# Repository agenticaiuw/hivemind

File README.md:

# Agentic Gadget

Unified monorepo for the Agentic Gadget hardware, firmware, local agent, cloud
relay, and Bluetooth audio bridge.

## Layout

- `firmware/nrf9160` — nRF9160 DK firmware (Zephyr/NCS)
- `firmware/esp32-airpods-bridge` — HUZZAH32 Bluetooth A2DP audio bridge
- `software/ai-pendant-simulator` — local Mac agent, cloud relay, and simulator
- `software/dashboard-sveltekit` — Mission Control dashboard (Cloudflare Worker)
- `hardware` — datasheets, electrical design, and KiCad sources
- `docs` — build guides and architecture notes

## Local agent

Keep private credentials in the repo-root `.env` (see `.env.example`). That file
is ignored by Git.

```sh
cd software/ai-pendant-simulator
npm install
npm test
npm run agent
```

## nRF9160 firmware

Build from `firmware/nrf9160` using the installed Nordic toolchain (NCS under
`/opt/nordic/ncs`). Build directories are intentionally not stored in this
repository. Private Kconfig values belong in the ignored
`firmware/nrf9160/secrets.conf` file and must be included with
`-DEXTRA_CONF_FILE=secrets.conf` when creating a fresh build.

```sh
source firmware/nrf9160/scripts/env.sh          # puts west/nrfutil on PATH
firmware/nrf9160/scripts/flash.sh --check       # verify probe + tools
# build (see docs/How_This_System_Runs.md), then:
firmware/nrf9160/scripts/flash.sh               # nrfutil → J-Link 960036581
```

ESP32 bridge: `firmware/esp32-airpods-bridge/flash.sh` (PlatformIO in `.venv`).

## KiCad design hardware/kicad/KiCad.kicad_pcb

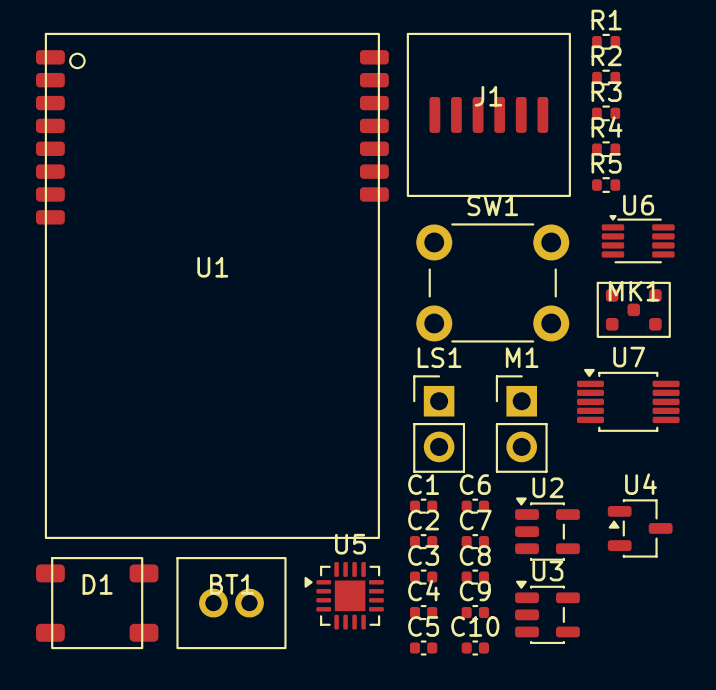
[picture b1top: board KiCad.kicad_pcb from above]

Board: 2 copper layers, 29 parts (0 on the bottom side), 26 nets, no tracks yet.

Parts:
BT1: LiPo_3V7; JST_PH_S2B
C1, C2: 4.7uF; C_0402_1005Metric
C3: 100uF; C_0402_1005Metric
C4: 10uF; C_0402_1005Metric
C5, C6, C8, C9: 1uF; C_0402_1005Metric
C7, C10: 0.1uF; C_0402_1005Metric
D1: SK6812
J1: USB4085_USB_C; USB4085-GF-A
LS1: Speaker_8ohm; PinHeader_1x02_P2.54mm_Vertical
M1: LRA_VLV101040A; PinHeader_1x02_P2.54mm_Vertical
MK1: T5837_PDM_mic; T5837
R1, R2: 5.1k; R_0402_1005Metric
R3: 2k; R_0402_1005Metric
R4, R5: 4.7k; R_0402_1005Metric
SW1: Button_B3F; SW_PUSH_6mm
U1: Icarus_SoM_nRF9160; Icarus_SoM
U2: MCP73831; SOT-23-5
U3: AP2112_3V3; SOT-23-5
U4: XC6206_1V8; SOT-23-3
U5: MAX98357A; QFN-16-1EP_3x3mm_P0.5mm_EP1.7x1.7mm
U6: TXB0102; VSSOP-8_2.3x2mm_P0.5mm
U7: DRV2605L; MSOP-10_3x3mm_P0.5mm

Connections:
+1V8: C6.1, C7.1, MK1.1, U4.3, U6.1
+3V3: C5.1, C9.1, R4.2, R5.2, U1.2, U3.5, U4.1, U6.2, U6.4, U7.1
BCLK: U1.4, U5.3
BTN_N: SW1.1, U1.12
CC1: J1.3, R1.1
CC2: J1.4, R2.1
DRV_OUTN: M1.2, U7.9
DRV_OUTP: M1.1, U7.8
GND: BT1.2, C1.2, C2.2, C3.2, C4.2, C5.2, C6.2, C7.2, C8.2, C9.2, C10.2, D1.2, J1.2, MK1.2, MK1.5, R1.2, R2.2, R3.2, SW1.2, U1.3, U2.2, U3.2, U4.2, U5.2, U6.3, U7.2, U7.5
I2S_DIN: U1.6, U5.5
LED_DIN: D1.3, U1.13
LRCLK: U1.5, U5.4
unnamed: R3.1, U2.5
unnamed: U1.14, U2.1
unnamed: C8.1, U7.3
unnamed: U1.11, U7.4
PDM_CLK_1V8: MK1.3, U6.5
PDM_CLK_3V3: U1.7, U6.7
PDM_DAT_1V8: MK1.4, U6.6
PDM_DAT_3V3: U1.8, U6.8
SCL: R5.1, U1.10, U7.6
SDA: R4.1, U1.9, U7.7
SPK_N: LS1.2, U5.9
SPK_P: LS1.1, U5.8
VBAT: BT1.1, C2.1, C3.1, C4.1, C10.1, D1.1, U1.1, U2.3, U3.1, U3.3, U5.1, U5.7
VBUS: C1.1, J1.1, U2.4
